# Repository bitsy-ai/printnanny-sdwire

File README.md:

# printnanny-sdwire
A modified version of Tizen SDWire https://wiki.tizen.org/SDWire

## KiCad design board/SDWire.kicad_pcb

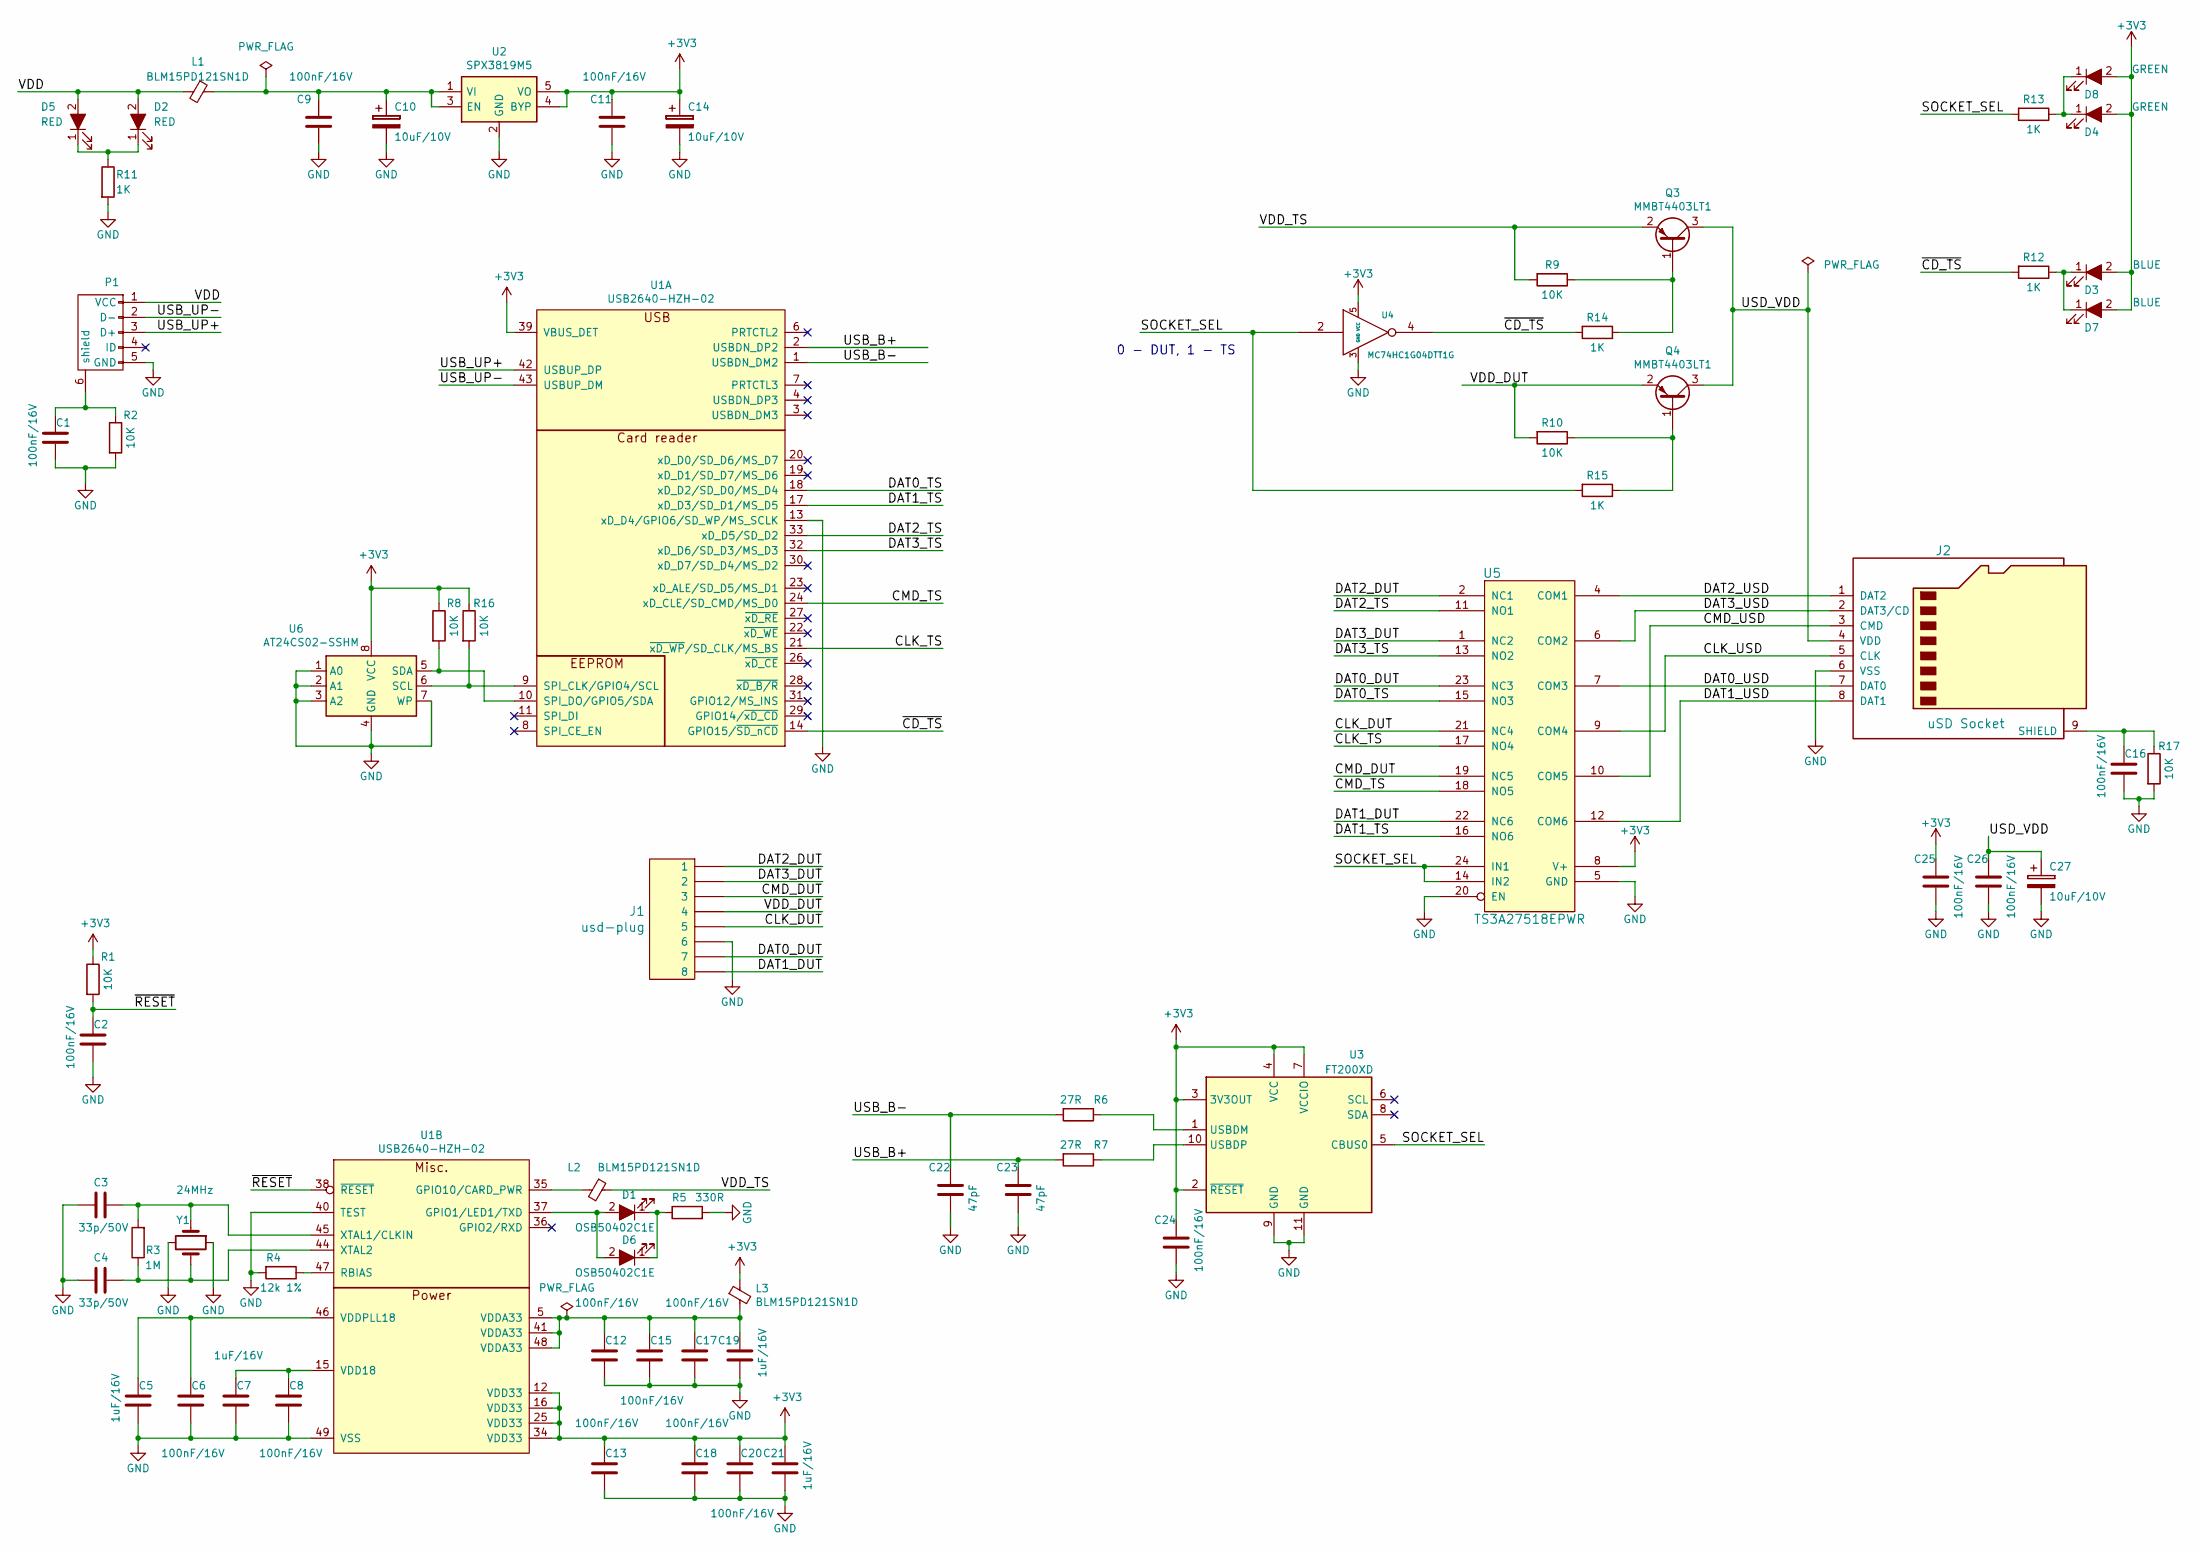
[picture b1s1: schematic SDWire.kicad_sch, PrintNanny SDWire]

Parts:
C1, C2, C6, C8, C9, C11, C12, C13, C15, C16, C17, C18, C20, C24, C25, C26: 100nF/16V; C_0402_1005Metric
C3, C4: 33p/50V; C_0402_1005Metric
C5, C7, C19, C21: 1uF/16V; C_0402_1005Metric
C10, C14, C27: 10uF/10V; CP_EIA-3216-18_Kemet-A_Pad1.58x1.35mm_HandSolder
C22, C23: 47pF; C_0402_1005Metric
D1, D6: OSB50402C1E; LED_0402_1005Metric
D2, D5: RED; LED_0402_1005Metric
D3, D7: BLUE; LED_0402_1005Metric
D4, D8: GREEN; LED_0402_1005Metric
J1: usd-plug; usd
J2: uSD Socket; microSD_HC_Molex_104031-0811
L1, L2, L3: BLM15PD121SN1D; L_0402_1005Metric
P1: USB_OTG_MICRO_USB; USB_Micro-B_Molex-105017-0001
Q3, Q4: MMBT4403LT1; SOT-23
R1, R2, R8, R9, R10, R16, R17: 10K; R_0402_1005Metric
R3: 1M; R_0402_1005Metric
R4: 12k 1%; R_0402_1005Metric
R5: 330R; R_0402_1005Metric
R6, R7: 27R; R_0402_1005Metric
R11, R12, R13, R14, R15: 1K; R_0402_1005Metric
U1: USB2640-HZH-02; QFN-48-1EP_7x7mm_Pitch0.5mm
U2: SPX3819M5; SOT-23-5
U3: FT200XD; DFN-10-1EP_3x3mm_P0.5mm_EP1.55x2.48mm
U4: MC74HC1G04DTT1G; SOT-23-5_HandSoldering
U5: TS3A27518EPWR; TSSOP-24
U6: AT24CS02-SSHM; SOIC-8_3.9x4.9mm_P1.27mm
Y1: 24MHz; Crystal_SMD_2520-4pin_2.5x2.0mm

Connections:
+3V3: C11.1, C13.1, C14.1, C18.1, C20.1, C21.1, C24.1, C25.1, D3.2 (A), D4.2 (A), D7.2 (A), D8.2 (A), L3.1, R1.1, R8.1, R16.1, U1.12 (VDD33), U1.16 (VDD33), U1.25 (VDD33), U1.34 (VDD33), U1.39 (VBUS_DET), U2.4 (BYP), U2.5 (VO), U3.2 (~RESET), U3.3 (3V3OUT), U3.4 (VCC), U3.7 (VCCIO), U4.5 (VCC), U5.8 (V+), U6.8 (VCC)
/CLK_DUT: J1.5, U5.21 (NC4)
/CLK_TS: U1.21 (~xD_WP/SD_CLK/MS_BS), U5.17 (NO4)
/CLK_USD: J2.5 (CLK), U5.9 (COM4)
/CMD_DUT: J1.3, U5.19 (NC5)
/CMD_TS: U1.24 (xD_CLE/SD_CMD/MS_D0), U5.18 (NO5)
/CMD_USD: J2.3 (CMD), U5.10 (COM5)
/DAT0_DUT: J1.7, U5.23 (NC3)
/DAT0_TS: U1.18 (xD_D2/SD_D0/MS_D4), U5.15 (NO3)
/DAT0_USD: J2.7 (DAT0), U5.7 (COM3)
/DAT1_DUT: J1.8, U5.22 (NC6)
/DAT1_TS: U1.17 (xD_D3/SD_D1/MS_D5), U5.16 (NO6)
/DAT1_USD: J2.8 (DAT1), U5.12 (COM6)
/DAT2_DUT: J1.1, U5.2 (NC1)
/DAT2_TS: U1.33 (xD_D5/SD_D2), U5.11 (NO1)
/DAT2_USD: J2.1 (DAT2), U5.4 (COM1)
/DAT3_DUT: J1.2, U5.1 (NC2)
/DAT3_TS: U1.32 (xD_D6/SD_D3/MS_D3), U5.13 (NO2)
/DAT3_USD: J2.2 (DAT3/CD), U5.6 (COM2)
/SOCKET_SEL: R13.2, R15.2, U3.5 (CBUS0), U4.2, U5.14 (IN2), U5.24 (IN1)
/USB_B+: C23.1, R7.2, U1.2 (USBDN_DP2)
/USB_B-: C22.1, R6.2, U1.1 (USBDN_DM2)
/USB_UP+: P1.3 (D+), U1.42 (USBUP_DP)
/USB_UP-: P1.2 (D-), U1.43 (USBUP_DM)
/USD_VDD: C26.1, C27.1, J2.4 (VDD), Q3.3 (C), Q4.3 (C)
/VDD: D2.2 (A), D5.2 (A), L1.2, P1.1 (VCC)
/VDD_DUT: J1.4, Q4.2 (E), R10.2
/VDD_TS: L2.1, Q3.2 (E), R9.2
/~CD_TS: R12.2, R14.2, U1.14 (GPIO15/~SD_nCD), U4.4
/~RESET: C2.1, R1.2, U1.38 (~RESET)
GND: C1.2, C2.2, C3.2, C4.2, C5.2, C6.2, C7.2, C8.2, C9.2, C10.2, C11.2, C12.2, C13.2, C14.2, C15.2, C16.2, C17.2, C18.2, C19.2, C20.2, C21.2, C22.2, C23.2, C24.2, C25.2, C26.2, C27.2, J1.6, J2.6 (VSS), P1.5 (GND), R2.2, R4.2, R5.2, R11.2, R17.2, U1.13 (xD_D4/GPIO6/SD_WP/MS_SCLK), U1.40 (TEST), U1.49 (VSS), U2.2 (GND), U3.9 (GND), U3.11 (GND), U4.3 (GND), U5.5 (GND), U5.20 (EN), U6.1 (A0), U6.2 (A1), U6.3 (A2), U6.4 (GND), U6.7 (WP), Y1.2, Y1.4
unnamed: C1.1, P1.6 (shield), R2.1
unnamed: C3.1, R3.2, U1.45 (XTAL1/CLKIN), Y1.1
unnamed: C4.1, R3.1, U1.44 (XTAL2), Y1.3
unnamed: C5.1, C6.1, U1.46 (VDDPLL18)
unnamed: C7.1, C8.1, U1.15 (VDD18)
unnamed: C9.1, C10.1, L1.1, U2.1 (VI), U2.3 (EN)
unnamed: C12.1, C15.1, C17.1, C19.1, L3.2, U1.5 (VDDA33), U1.41 (VDDA33), U1.48 (VDDA33)
unnamed: C16.1, J2.9 (SHIELD), R17.1
unnamed: D1.1 (K), D6.1 (K), R5.1
unnamed: D1.2 (A), D6.2 (A), U1.37 (GPIO1/LED1/TXD)
unnamed: D2.1 (K), D5.1 (K), R11.1
unnamed: D3.1 (K), D7.1 (K), R12.1
unnamed: D4.1 (K), D8.1 (K), R13.1
unnamed: L2.2, U1.35 (GPIO10/CARD_PWR)
unnamed: Q3.1 (B), R9.1, R14.1
unnamed: Q4.1 (B), R10.1, R15.1
unnamed: R4.1, U1.47 (RBIAS)
unnamed: R6.1, U3.1 (USBDM)
unnamed: R7.1, U3.10 (USBDP)
unnamed: R8.2, U1.10 (SPI_DO/GPIO5/SDA), U6.5 (SDA)
unnamed: R16.2, U1.9 (SPI_CLK/GPIO4/SCL), U6.6 (SCL)

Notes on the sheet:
0 - DUT, 1 - TS

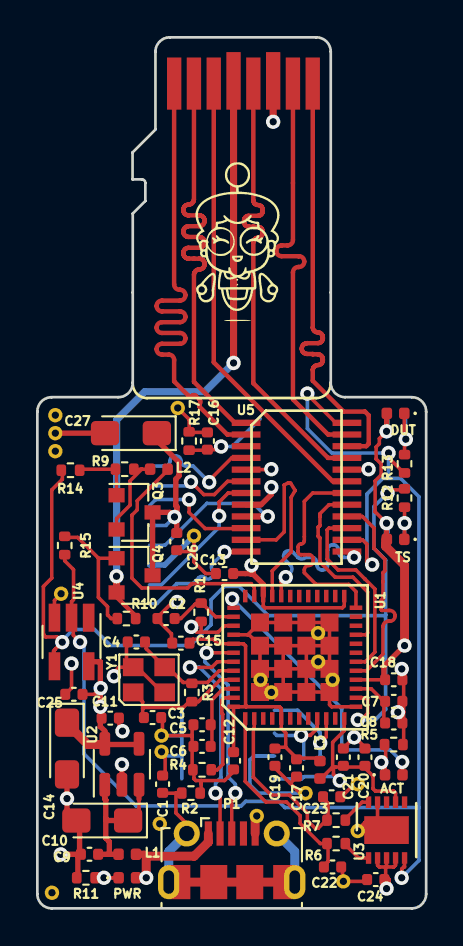
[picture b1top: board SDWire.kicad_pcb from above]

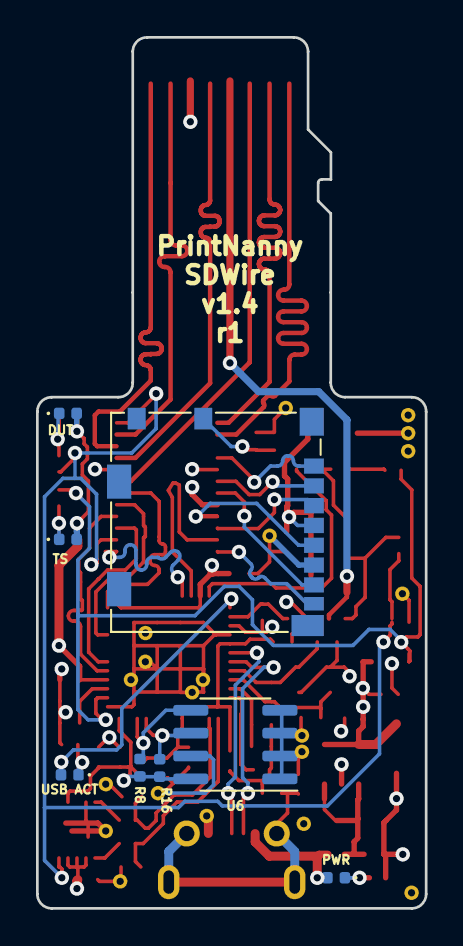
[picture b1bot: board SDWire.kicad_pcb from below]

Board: 4 copper layers, 21.6 x 48.4 mm, 67 parts (8 on the bottom side), 52 nets.

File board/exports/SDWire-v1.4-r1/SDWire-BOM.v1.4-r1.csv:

"Source:","printnanny-sdwire/board/SDWire.kicad_sch"
"Date:","Mon Aug 22 21:12:53 2022"
"Tool:","Eeschema 6.0.6"
"Generator:","/usr/share/kicad/plugins/bom_csv_grouped_by_value_with_fp.py"
"Component Count:","65"

"Ref","Qnty","Value","Cmp name","Footprint","Description","Vendor"
"C1, C2, C6, C8, C9, C11, C12, C13, C15, C17, C18, C20, C24, C25, C26, ","15","100nF/16V","C","Capacitor_SMD:C_0402_1005Metric","",""
"C22, C23, ","2","47pF","C","Capacitor_SMD:C_0402_1005Metric","",""
"C5, C7, C19, C21, ","4","1uF/16V","C","Capacitor_SMD:C_0402_1005Metric","",""
"C3, C4, ","2","33p/50V","C","Capacitor_SMD:C_0402_1005Metric","",""
"C10, C14, C27, ","3","10uF/10V","CP","Capacitor_Tantalum_SMD:CP_EIA-3216-18_Kemet-A_Pad1.58x1.35mm_HandSolder","",""
"R11, R12, R13, R14, R15, ","5","1K","R","Resistor_SMD:R_0402_1005Metric","",""
"R1, R2, R8, R9, R10, R16, ","6","10K","R","Resistor_SMD:R_0402_1005Metric","",""
"R3, ","1","1M","R","Resistor_SMD:R_0402_1005Metric","",""
"R4, ","1","12k 1%","R","Resistor_SMD:R_0402_1005Metric","",""
"R5, ","1","330R","R","Resistor_SMD:R_0402_1005Metric","",""
"R6, R7, ","2","27R","R","Resistor_SMD:R_0402_1005Metric","",""
"D1, D6, ","2","OSB50402C1E","LED_ALT","LED_SMD:LED_0402_1005Metric","",""
"D2, D5, ","2","RED","LED_ALT","LED_SMD:LED_0402_1005Metric","",""
"D3, D7, ","2","BLUE","LED_ALT","LED_SMD:LED_0402_1005Metric","",""
"D4, D8, ","2","GREEN","LED_ALT","LED_SMD:LED_0402_1005Metric","",""
"L1, L2, L3, ","3","BLM15PD121SN1D","Ferrite_Bead_Small_1","Inductor_SMD:L_0402_1005Metric","",""
"J1, ","1","usd-plug","usd-plug","connectors:usd","",""
"J2, ","1","uSD Socket","Micro_SD_Card","Connector_Card:microSD_HC_Molex_104031-0811","Micro SD Card Socket",""
"P1, ","1","USB_OTG_MICRO_USB","USB_OTG_MICRO_USB","Connector_USB:USB_Micro-B_Molex-105017-0001","",""
"Q3, Q4, ","2","MMBT4403LT1","MMBT4403LT1","TO_SOT_Packages_SMD:SOT-23","",""
"U1, ","1","USB2640-HZH-02","USB2640","mux-footprints:QFN-48-1EP_7x7mm_Pitch0.5mm","",""
"U2, ","1","SPX3819M5","SPX3819M5","Package_TO_SOT_SMD:SOT-23-5_HandSoldering","",""
"U3, ","1","FT200XD","FT200XD","Package_DFN_QFN:DFN-10-1EP_3x3mm_P0.5mm_EP1.55x2.48mm","Full Speed USB to I2C Bridge, DFN-10",""
"U4, ","1","MC74HC1G04DTT1G","74AHC1G14","Package_TO_SOT_SMD:SOT-23-5_HandSoldering","",""
"U5, ","1","TS3A27518EPWR","TS3A27518E","mux-footprints:TSSOP-24","",""
"U6, ","1","AT24CS02-SSHM","AT24CS02-SSHM","Package_SO:SOIC-8_3.9x4.9mm_P1.27mm","I2C Serial EEPROM, 2Kb (256x8) with Unique Serial Number, SO8",""
"Y1, ","1","24MHz","4pinCrystal","mux-footprints:Crystal_SMD_2520-4pin_2.5x2.0mm","",""

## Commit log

2022-09-02 Tizen SDWire is Apache-2.0 license
2022-09-02 Add 3D model renders
2022-09-02 Add SDWire-v1.4-r1 gerbers
    Closes: https://github.com/bitsy-ai/printnanny-sdwire/issues/2
2022-09-02 Initial commit of PrintNanny-SDWire-v1.4-r1
2022-09-03 add PrintNanny-SDWire-v1.4-r1-schematic.pdf
2022-09-22 Add SDWire utility
    Imported verbatim from
    https://git.tizen.org/cgit/tools/testlab/sd-mux/tree/src/main.cpp?id=9dd189d973da64e033a0c5c2adb3d94b23153d94
2022-12-29 Add vcpkg submodule
2022-12-29 Add vcpkg github action
2022-12-29 Add vcpkg spec
2023-01-14 CMake: Search for vcpkg deps manually
2023-01-14 Only ftdi1 and popt are required
2023-01-14 Update vcpkg submodule
2023-01-14 optional libusb and libconfuse
2023-01-14 Port unix-specific usleep to windows
2023-01-14 Windows compat for strcasecmp
2023-01-17 error LNK2019: unresolved external symbol "struct poptOption * poptHelpOptions"
2023-01-17 Upload artifact

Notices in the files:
board/SDWire.kicad_pcb:
Copyright (c) 2022 Bitsy AI Labs LLC. All Rights Reserved
Copyright (c) 2016 Samsung Electronics Co., Ltd All Rights Reserved
